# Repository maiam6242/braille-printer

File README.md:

# Portabraille Printer by Team Dot Dot Dot

### The Portabraille Printer is a portable and accessible braille printer which enables users who are visually impaired to quickly and easily produce accurate, high quality braille.

## Table of Contents
- [Introduction](#Introduction "Introduction")
- [This Repository](#This-Repository "This Repository") 
- [Requirements](#Requirements "Requirements")
- [Installation](#Installation "Installation")  
- [Feedback](#Feedback "Feedback") 
- [Team](#Team "Team")  
- [Acknowledgments](#Acknowledgments "Acknowledgments") 

## Introduction
The Portabraille Printer is a device that takes in an English text input, translates that text into uncontracted braille, then prints said braille text on braille paper. It is a low cost product that aims to allow people who are visually impaired to create braille quickly, with applications ranging from producing quick meeting notes to creating accessible promotional materials on the fly. The printer is light, with handles for easy transportation, and has an easy-to-use interface with both braille and English text, creating a user friendly experience for those who are visually impaired or blind. Text documents can be fed to the printer via either the Portabraille Portal on the Portabraille Network or by plugging in a USB. 

## This Repository

This repository contains the vast majority of the files which we created over the course of this project. It is split into two main folders: [Software](https://github.com/maiam6242/braille-printer/tree/master/Software "Software Forlder") and [Firmware](https://github.com/maiam6242/braille-printer/tree/master/Firmware "Firmware Folder"), each of which houses artifacts for the respective subsystems. These folders are also split into multiple subfolders. There is also a [Branding](https://github.com/maiam6242/braille-printer/tree/master/Branding "Branding Folder") folder which has the logo that we used on our shirts.

On the software side, the [Text Side Folder](https://github.com/maiam6242/braille-printer/tree/master/Software/Text%20Side "Text Side Folder") has software that takes a text input, converts it to a braille output and sends it to the firmware. All of this is written in Python. The [Physical Interface Folder](https://github.com/maiam6242/braille-printer/tree/master/Software/Physical%20Interface "Physical Interface Folder") contains software written in Python and designs created in Illustrator which relate to the user interface on our printer. The web interface written in html and designed in Illustrator is in the [Web Interface Folder](https://github.com/maiam6242/braille-printer/tree/master/Software/Web%20Interface "Web Interface Folder"). The [Recognizing Input Folder](https://github.com/maiam6242/braille-printer/tree/master/Software/Recognizing%20Input) includes all of the scripts in bash and Python that allow us to take in USB or Wifi input and the [README Resources Folder](https://github.com/maiam6242/braille-printer/tree/master/Software/README%20Resources "README Resources Folder") contains all of the files referenced in this document. Lastly, the [Startup Scripts Folder](https://github.com/maiam6242/braille-printer/tree/master/Software/StartupScripts "Startup Scripts Folder") contains the scripts which need to be run on the Raspberry Pi to ensure that our software and network run on startup. 

In the firmware folder, the firmware that controls the way paper is loaded and how solenoids act is in the [Arduino Firmware Folder](https://github.com/maiam6242/braille-printer/tree/master/Firmware/Arduino%20Firmware "Arduino Firmware Folder"). All of our firmware is written in C++. The [PCB Folder](https://github.com/maiam6242/braille-printer/tree/master/Firmware/PCB "PCB Folder") contains all of the artifacts from our PCB design.

## Requirements

- Python 3 (or newer)
- Raspberry Pi 3B, 3B+ or 4
- Rasbian Jesse (or newer)

## Installation
The software that runs on the Portabraille Printer has a variety of dependencies. The [startup bash script](https://github.com/maiam6242/braille-printer/blob/master/startup.bash "Startup Bash Script") automatically installs all of the dependencies from all components of our firmware and software. Instructions and code samples for installing these dependencies individually are below. 

#### Python Text to Speech
The following bash command installs pyttsx3, a text to speech library for Python. 
``` bash
pip3 install pyttsx3
```

#### NumPy
The following bash command installs NumPy, a package for computing with Python. 
``` bash
pip3 install numpy
```

#### GPIO Zero
The following bash command installs GPIO Zero, a library for interfacing GPIO devices with Raspberry Pi.
``` bash
pip3 install gpiozero
```

#### PySerial
The following bash command installs pySerial, a module for accessing the serial port.
``` bash
pip3 install pyserial
```

#### eSpeak
The following bash command installs eSpeak, an open source speech synthesizer for Linux and Windows.
```bash
sudo apt-get install espeak
```

#### Flask
The following bash command installs Flask, a microweb framework.
```bash
pip3 install Flask
```

## Feedback
We would love to hear feedback on this project! Feel free to [email us](mailto:mmaterman@olin.edu "mmaterman@olin.edu") or [submit an issue](https://github.com/maiam6242/braille-printer/issues/new/choose "New Issue Request"). If you are interested in contributing to this project or chatting about it in general, please don't hesitate to [email us](mailto:mmaterman@olin.edu "mmaterman@olin.edu") here!

## Team
Annie Tor [@ator1](https://github.com/ator1 "Annie's GitHub")   
Colin Snow [@colinmsnow](https://github.com/colinmsnow "Colin's GitHub")  
Maia Materman [@maiam6242](https://github.com/maiam6242 "Maia's GitHub")  
Megan Ku [@megku4u](https://github.com/megku4u "Megan's GitHub")  
Nathan Weil [@NWeil](https://github.com/NWeil "Nathan's GitHub")  

## Acknowledgments
Thanks to the Fall 2019 Principles of Engineering Teaching Team, Professors Aaron Hoover, Amon Millner, Siddhartan Govindasamy and Stan Reifel for their support and assistance throughout this process. Additional thanks to Frank Ventura, Jerry Berrier, David Kingsbury, John Smith, and Jeanette Kutash and for their INDISPENSABLE help during this adventure. The insights they provided about our design helped us craft a product that is actually usable. Lastly, thank you to the MIT Visually Impaired and Blind User Group for hosting us and letting us pick their brains regarding our printer and braille in general.

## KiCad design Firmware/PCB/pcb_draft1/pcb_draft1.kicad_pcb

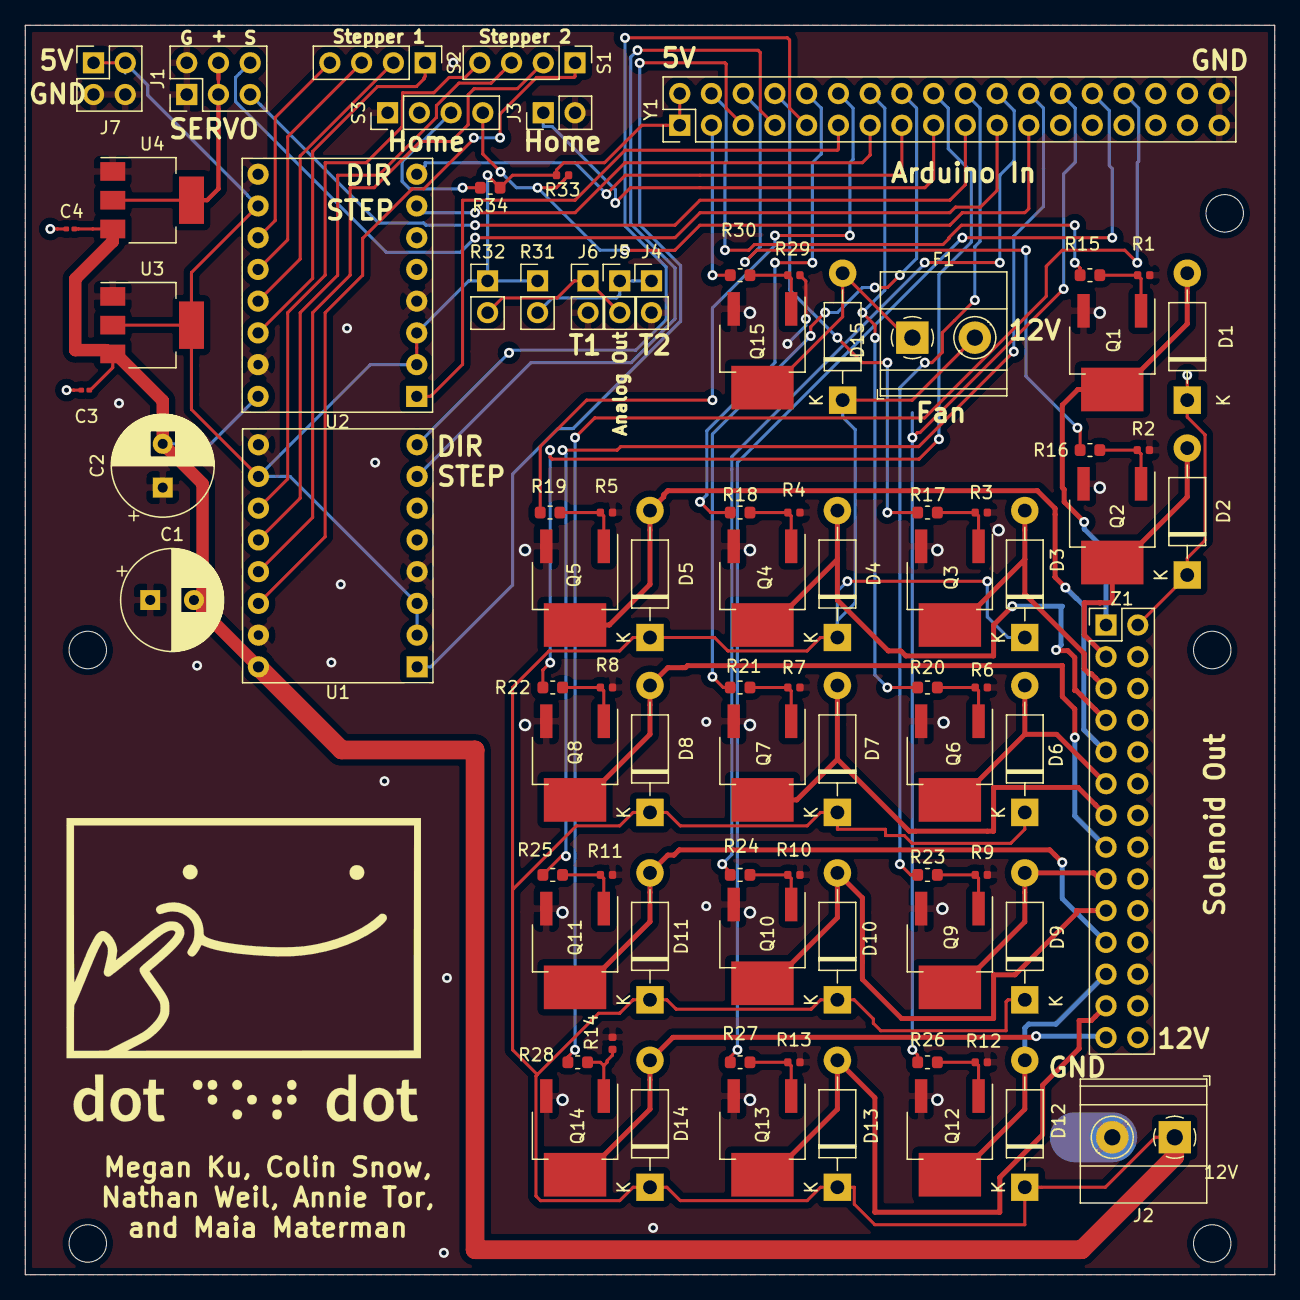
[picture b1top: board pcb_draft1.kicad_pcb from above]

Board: 2 copper layers, 100.0 x 100.0 mm, 86 parts (0 on the bottom side), 70 nets.

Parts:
12V: MountingHole_3mm
C1, C2: C; CP_Radial_D8.0mm_P3.50mm
C3, C4: C_0201_0603Metric
D1, D2, D3, D4, D5, D6, D7, D8, D9, D10, D11, D12, D13, D14, D15: 1N4003; D_DO-41_SOD81_P10.16mm_Horizontal
F1: Fan_Screw_Terminal A97996-ND; TerminalBlock_Phoenix_MKDS-1,5-2_1x02_P5.00mm_Horizontal
J1: RollerServos; PinHeader_2x03_P2.54mm_Vertical
J2: 12V_Power A97996-ND; TerminalBlock_Phoenix_MKDS-1,5-2_1x02_P5.00mm_Horizontal
J3: HomeSwitch; PinHeader_1x02_P2.54mm_Vertical
J4: Therm1; PinHeader_1x02_P2.54mm_Vertical
J5: ArdAnalogTherm; PinHeader_1x02_P2.54mm_Vertical
J6: Therm2; PinHeader_1x02_P2.54mm_Vertical
J7: Conn_02x02_Odd_Even; PinHeader_2x02_P2.54mm_Vertical
Q1, Q2, Q3, Q4, Q5, Q6, Q7, Q8, Q9, Q10, Q11, Q12, Q13, Q14, Q15: DMN6140L; SOT-223-edited
R1, R2, R3, R4, R5, R6, R7, R8, R9, R10, R11, R12, R13, R14, R29: 10K_Ohm_R; R_0402_1005Metric
R15, R16, R17, R18, R19, R20, R21, R22, R23, R24, R25, R26, R27, R28, R30: 200_Ohm_R; R_0603_1608Metric
R31, R32: ThermistorR; PinHeader_1x02_P2.54mm_Vertical
R33: 2.7k_Ohm_Res; R_0402_1005Metric
R34: 250_Ohm_Resistor; R_0603_1608Metric
S1: StepperMotor1; PinHeader_1x04_P2.54mm_Vertical
S2: StepperMotor2; PinHeader_1x04_P2.54mm_Vertical
S3: PaperHome; PinHeader_1x04_P2.54mm_Vertical
U1, U2: STSPIN820; stepper_driver
U3: AMS1117-5.0 RasPi; SOT-223-3_TabPin2
U4: AMS1117-5.0 Servo; SOT-223-3_TabPin2
Y1: Arduino_Mega_Bottom_Pins1; PinHeader_2x18_P2.54mm_Vertical
Z1: SolenoidOut; PinHeader_2x14_P2.54mm_Vertical

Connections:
5V: J7.1, J7.2, R31.1, R32.1, R33.2, R34.1, U1.2, U1.3, U1.15, U2.2, U2.3, U2.15, U3.2, Y1.1, Y1.2
12V: C1.2, C2.2, D1.1, D2.1, D3.1, D4.1, D5.1, D6.1, D7.1, D8.1, D9.1, D10.1, D11.1, D12.1, D13.1, D14.1, D15.1, F1.2, J2.1, U1.9, U2.9, U3.3, U4.3, Z1.2, Z1.4, Z1.6, Z1.8, Z1.10, Z1.12, Z1.14, Z1.16, Z1.18, Z1.20, Z1.22, Z1.24, Z1.26, Z1.28
Fan: R30.1, Y1.3
GND: C1.1, C2.1, J1.1, J1.2, J2.2, J3.2, J4.2, J6.2, J7.3, J7.4, Q1.3, Q2.3, Q3.3, Q4.3, Q5.3, Q6.3, Q7.3, Q8.3, Q9.3, Q10.3, Q11.3, Q12.3, Q13.3, Q14.3, Q15.3, R1.1, R2.1, R3.1, R4.1, R5.1, R6.1, R7.1, R8.1, R9.1, R10.1, R11.1, R12.1, R13.1, R14.1, R29.1, S3.1, S3.2, U1.4, U1.10, U1.16, U2.4, U2.10, U2.16, U3.1, U4.1, Y1.35, Y1.36
HomeSwitch: J3.1, Y1.17
unnamed: D1.2, Q1.2, Z1.1
unnamed: D2.2, Q2.2, Z1.3
unnamed: D3.2, Q3.2, Z1.5
unnamed: D4.2, Q4.2, Z1.7
unnamed: D5.2, Q5.2, Z1.9
unnamed: D6.2, Q6.2, Z1.11
unnamed: D7.2, Q7.2, Z1.13
unnamed: D8.2, Q8.2, Z1.15
unnamed: D9.2, Q9.2, Z1.17
unnamed: D10.2, Q10.2, Z1.19
unnamed: D11.2, Q11.2, Z1.21
unnamed: D12.2, Q12.2, Z1.23
unnamed: D13.2, Q13.2, Z1.25
unnamed: D14.2, Q14.2, Z1.27
unnamed: D15.2, F1.1, Q15.2
unnamed: J4.1, J5.1, R31.2
unnamed: J5.2, J6.1, R32.2
unnamed: Q1.1, R1.2, R15.2
unnamed: Q2.1, R2.2, R16.2
unnamed: Q3.1, R3.2, R17.2
unnamed: Q4.1, R4.2, R18.2
unnamed: Q5.1, R5.2, R19.2
unnamed: Q6.1, R6.2, R20.2
unnamed: Q7.1, R7.2, R21.2
unnamed: Q8.1, R8.2, R22.2
unnamed: Q9.1, R9.2, R23.2
unnamed: Q10.1, R10.2, R24.2
unnamed: Q11.1, R11.2, R25.2
unnamed: Q12.1, R12.2, R26.2
unnamed: Q13.1, R13.2, R27.2
unnamed: Q14.1, R14.2, R28.2
unnamed: Q15.1, R29.2, R30.2
unnamed: R15.1, Y1.4
unnamed: R16.1, Y1.6
unnamed: R17.1, Y1.8
unnamed: R18.1, Y1.10
unnamed: R19.1, Y1.12
unnamed: R20.1, Y1.14
unnamed: R21.1, Y1.16
unnamed: R22.1, Y1.18
unnamed: R23.1, Y1.20
unnamed: R24.1, Y1.22
unnamed: R25.1, Y1.24
unnamed: R26.1, Y1.26
unnamed: R27.1, Y1.28
unnamed: R28.1, Y1.30
unnamed: R34.2, S3.3
unnamed: S1.1, U1.11
unnamed: S1.2, U1.12
unnamed: S1.3, U1.13
unnamed: S1.4, U1.14
unnamed: S2.1, U2.11
unnamed: S2.2, U2.12
unnamed: S2.3, U2.13
unnamed: S2.4, U2.14
PaperHome: R33.1, S3.4, Y1.23
Servo1: J1.5, Y1.19
Servo2: J1.6, Y1.21
Servo5V: J1.3, J1.4, U4.2
StD1Dir: U1.8, Y1.9
StD1En: U1.1, Y1.5
StD1St: U1.7, Y1.7
StD2Dir: U2.8, Y1.15
StD2En: U2.1, Y1.11
StD2St: U2.7, Y1.13

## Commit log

2019-10-18 readme title
2019-10-18 started the blog, baby!
2019-10-18 10/17 image
2019-10-18 Revert "10/17 image"
    This reverts commit a59204c7930a4e0e961dd292eb46c740539d4f69.
2019-10-18 branches, be my friend
2019-10-18 what if this just worked?
2019-10-18 maybe??
2019-10-18 Update Site ReadMe
2019-10-18 reading and opening text files
2019-10-20 coding? coding!
2019-10-20 what if code just liked me? Asking for a friend...
2019-10-21 setting up new class
2019-10-21 created translator dictionary
2019-10-21 making things modular is hard. So is typing. What a wild ride. :penguin:
2019-10-22 :astonished:
2019-10-22 Frequency testing code
2019-10-22 :guardsman:
2019-10-22 :flushed:
2019-10-22 Working but ugly code to interpret capitals and numbers
2019-10-22 :smile:
2019-10-22 :sunglasses:
2019-10-22 :confused:
2019-10-22 :blush:
2019-10-22 question:
2019-10-22 :question:
2019-10-22 Add unit tests and other code during LiveShare
2019-10-22 Translator passes all unit tests and split_into_lines is functioning correctly
2019-10-22 Add setter for line number
2019-10-22 :book:
2019-10-23 ahhhhh
2019-10-27 First work on firmware creating stepper class
2019-10-27 Stepper controller with working forward-back control and goTo functions
2019-10-27 Horizontal stepper class with working home and go to character methods
2019-10-27 Full servo control with both horizontal and paper stepper classes
2019-10-27 Move classes to separate documents
2019-10-28 Starting work on gcode commands
2019-10-28 Probable implementation of 5 GCODE commands but arduino giving trouble
2019-10-28 Functions working but problems with serial, reusing serial pins suspected
2019-10-28 Potentially fixed errors by initializing classes within loop
2019-10-28 Working controller but with classes defined in loop
2019-10-28 Controlling stepper successfully for a moment
2019-10-29 Works for firing at least one solenoid
2019-10-29 Working for both steppers and all 14 solenoids
2019-10-29 Add first draft of PCB
2019-10-29 Finish wiring for PCB First Draft
2019-10-29 Add GND to Mode Pins
2019-10-29 Add footprints to most components (need to connect drivers)
2019-10-29 Add custom footprint for driver
2019-10-29 Add custom footprint for mosfet
2019-10-30 Steppers move with acceleration
2019-10-30 Fixed critical errors with misdefinition fo AccelStepper class and passing copy of class instead of pointer to the interpreter
2019-10-30 Add enable support and clean extra lines
2019-10-31 Fix misdefinition of solenoid pins - stable release with motors and solenoids working
2019-11-01 Update PCB
2019-11-01 will this work? maybe!
2019-11-01 Add machine read mode to make interface to raspi easy
2019-11-02 ahhhhhhh
2019-11-02 uncomfy
2019-11-03 brooo what if I wrote commit messages that were useful?! ...novel
2019-11-03 testing github
2019-11-03 stack lied to me!
2019-11-03 let's see what github is up to
2019-11-06 Update PCB to add fan and thermistor (needs to be fixed)
2019-11-07 maybe using github is a thing that should be done. unclear.
2019-11-08 Don't totally hate python (maybe?)
2019-11-08 good code practices? who's she?
2019-11-08 add first draft png
2019-11-08 Convert positioning to mm and add ability to request position
2019-11-08 Everyday likeable gal alert!
2019-11-08 Hello grandmother!
2019-11-08 ahhhhhhhhh
2019-11-08 FINISHED THE INITAL SOFTWARE STUFF (need to still test split_lines in drawable?)
2019-11-09 Set semi-accurate steps per mm and fix problem with last solenoid firing
2019-11-09 Fix speeds and accelerations for better paper movement
2019-11-10 Add interrupt sensor to home paper
2019-11-10 Update PCB with accurate connector types
2019-11-10 add new netlist
2019-11-11 Fix x axis homing
2019-11-12 Add footprints and finalize layout - need to add 10kohm resistors
2019-11-12 Recast movement inputs as double to allow for sub-milimeter precision
2019-11-12 Attempt to fix errors in non ASCI characters
2019-11-13 Oof, Integration
2019-11-14 Run traces for preliminarily finished board
2019-11-14 AHHHHHHHHHHH
2019-11-14 So found a massive logic bug which not has to be figured out in terms of the order we get the current position and write things, but serail is working and paper is movin
2019-11-14 fix few unconnected pads
2019-11-15 Fix silkscreen and add holes
2019-11-15 Lookminto position errors
2019-11-15 Look into position errors and add notes to physical
2019-11-15 Not sure what these are...
2019-11-15 Taking things out of here
2019-11-15 Getting rid of more things
2019-11-15 Add gitignore
2019-11-15 Ahh GitHub!
2019-11-15 hopefully fixed
2019-11-15 so much to delete
2019-11-15 hopefully done?
2019-11-15 Add interface class
2019-11-15 Splitting pages is the worst
2019-11-16 Work on Interface class
2019-11-16 I hate python ahhhhhhh
2019-11-16 Ugh code, who even likes you? Asking for a friend...
2019-11-16 Changed whole structure of matrix to make it easier to understand and keep lines
2019-11-16 adding logo for readme
2019-11-16 Started Creating README
2019-11-16 Finished writing and implementing write_row function
2019-11-16 Annie killed it!! Annie made all the things!! Yessss we love Annie so much!
2019-11-18 what if it were already break? asking for a friend...
2019-11-18 writing documentation is fun!
2019-11-18 oops some minor readme changes
2019-11-19 for loops? for loops.
2019-11-19 Testing with interface
2019-11-19 done? maybe?
2019-11-19 :cookie:
2019-11-19 I need file paths, my dude
2019-11-19 Just when I started to understand python
2019-11-19 Uploading website homepage design
2019-11-19 making bash our friend
2019-11-19 trying to make github my friend... it's rough
2019-11-19 Add ability to get files from usb (untested)
2019-11-19 How is there more stuff?
2019-11-19 maybe this will work?
2019-11-19 Less creepy voices?
2019-11-19 Add simple flask app to download files
2019-11-19 Trying to find voices that aren't creepy
2019-11-19 Testing ai to html script
2019-11-19 Fix upload directory for cross-platform integration
2019-11-21 adding stuff to make ai to html file work
2019-11-21 making all sorts of new friends
2019-11-21 uploading website testing files
2019-11-21 :cold:
2019-11-21 do raspis like me? of course not
2019-11-21 ahhhhhh
2019-11-21 or what? what...
2019-11-21 Pushing any new board stuff
2019-11-21 so much code
2019-11-21 Attempt to flip paper stepper direction
2019-11-21 I think it's working? Maybe?
2019-11-22 good joke
2019-11-22 maybe actually do things
2019-11-22 at least this isn't crimping?
2019-11-22 Switch arduino pins for PCB
2019-11-22 Maia 0. Raspi 3? 4? 40,000? Unclear
2019-11-22 more documentation, oh the joy
2019-11-22 updating README??
2019-11-22 small todos
2019-11-23 Add timeout to serial read
2019-11-23 Not an ECE or anything, but pretty dang proud
2019-11-23 GitHub has a renamed thing? This is truly wild
2019-11-23 yooo took out those delays, speeeeeddd demons
2019-11-23 At least it does the thing? Maybe? :grimacing:
2019-11-23 :ant:
2019-11-23 Ugh my last git commit in this folder was so good. Go check it out, now it's rewritten. Bum...
2019-11-24 coding in text editors is a time
2019-11-24 Update issue templates
    GitHub wanted issue templates, they seem like fun!
2019-11-24 Oh indentation
2019-11-24 This interface is a huge pain
2019-11-24 little things
2019-11-29 idea: candle but you light it from the bottom
2019-11-29 idea: dogs but chill and not as wet
2019-12-01 How is break already over?
2019-12-03 swapped button port for cancel and print buttons; removedp print statements
2019-12-03 maybe things will be our friend? A gal can definitely dream
2019-12-03 Aghhh why are state changes so lame?
2019-12-03 Remove merge conflict text
2019-12-03 Change import interface line 7
2019-12-03 changed little readme things
2019-12-03 Don't be alarmed
2019-12-03 Working on making code look good
2019-12-03 Changing the things
2019-12-03 Deleting so many things, so much power
2019-12-03 This is about to be a complete mess
2019-12-03 Ughhhh
2019-12-03 Did this happen?
2019-12-03 Taking out silly test
2019-12-03 Add attributes to account for state changes in buttons and switches:
2019-12-03 Fixed some silly readme things
2019-12-03 Added runAndWait() functions after say() for each speech command
2019-12-03 Web Interface Stuff
2019-12-04 Add functionality to load files from the web interface
2019-12-04 Forcing sudo upon the masses
2019-12-04 'Colinnnnnnn' --Maia
2019-12-04 Add simple selection of files to be printed
2019-12-05 Add test exit handler
2019-12-05 Documenting code to get inputs
2019-12-05 :ant: gonna work on my computer
2019-12-05 things aren't working, but nothing new there
2019-12-05 Yayyy something is working, this is wild
2019-12-05 :sparkles:
2019-12-05 everything but the play pause is being kind. Tragic? Or exciting? Take your pick
2019-12-05 trying all sorts of wacky stuff
2019-12-05 Startup scripts
2019-12-05 whatever maia didn't push
2019-12-05 added print statements so I know where they're coming from
2019-12-05 Add filename to print statements
2019-12-05 Fix comment error - MK
2019-12-05 Edit startup script
2019-12-06 Please make code make sense
2019-12-06 Streamlining interface
2019-12-06 quick website update
2019-12-06 So close
2019-12-06 please workkk
2019-12-06 vs code here we come
2019-12-06 Please work
2019-12-06 Maia 1. Double Quotes 0. Doing things that really matter also 0
2019-12-06 Add checks for buttons throuought code
2019-12-06 Pleasee
2019-12-06 landing page things
2019-12-06 do you prefer this
2019-12-06 what about this
2019-12-06 Update upload.html
    how about now
2019-12-06 Work from night 0f 12-5
2019-12-06 Some documentation
2019-12-06 Make led run when error signaled
2019-12-06 Files from friday class
2019-12-06 Add choices for usb printing
2019-12-06 creating team page
2019-12-06 Adjust paper home position
2019-12-08 Changing some of the voice commands
2019-12-08 initial bare bones of the website
2019-12-08 getting links to work
2019-12-08 getting that sweet dropdown working
2019-12-08 read
2019-12-08 adding some website graphics!
2019-12-08 fixing upload page formatting issues
2019-12-09 Added t-shirt file
2019-12-09 Fixing sound switch
2019-12-09 adding blog
2019-12-09 Update blog.html
    linking to first blog
2019-12-10 are we really done now?
2019-12-10 changing tab order and adding a place for system overviews
2019-12-10 changing tabs and fixing homepage formatting
2019-12-11 firmware
2019-12-11 it's not early
2019-12-11 small
2019-12-11 now it's later
2019-12-11 bios not blogs
2019-12-11 adding sprint pages
2019-12-11 sprint1 closer?
2019-12-11 starting?
2019-12-11 firmware cal
2019-12-11 adding design component to sprints, updating team page formatting, adding links for resources
2019-12-11 fixing some formatting issues
2019-12-11 adding content
2019-12-12 Oops, forgot we weren't doing this in the code
2019-12-13 Buster!
2019-12-13 Add Firmware User Guide
2019-12-13 some evidence of progress so you know I'm working
2019-12-13 done with sprint 1
2019-12-13 finishing instructions page
2019-12-13 legitimately the worst night of of my life
2019-12-13 bolding shit
2019-12-13 did I make it more responsive?
2019-12-13 Revert "did I make it more responsive?"
    This reverts commit 81891782cd90f9d0ccc87a16f3d6b4ad5a7a865f.
2019-12-13 adding system files. love, annie
2019-12-13 adding sprint 2 page
2019-12-13 made borders scale!
2019-12-13 they told me to push so I am
2019-12-13 Resolving merge conflicts
2019-12-13 a new commit message
2019-12-13 wowie
2020-01-08 Fixing image alt texts and some website formatting issues
2020-01-17 fixing system overview graphic
